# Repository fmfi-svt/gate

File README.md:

This repo is no longer used -- see [github.com/fmfi-svt-deadlock](https://github.com/fmfi-svt-deadlock) for Project Deadlock (formerly Project Gate).

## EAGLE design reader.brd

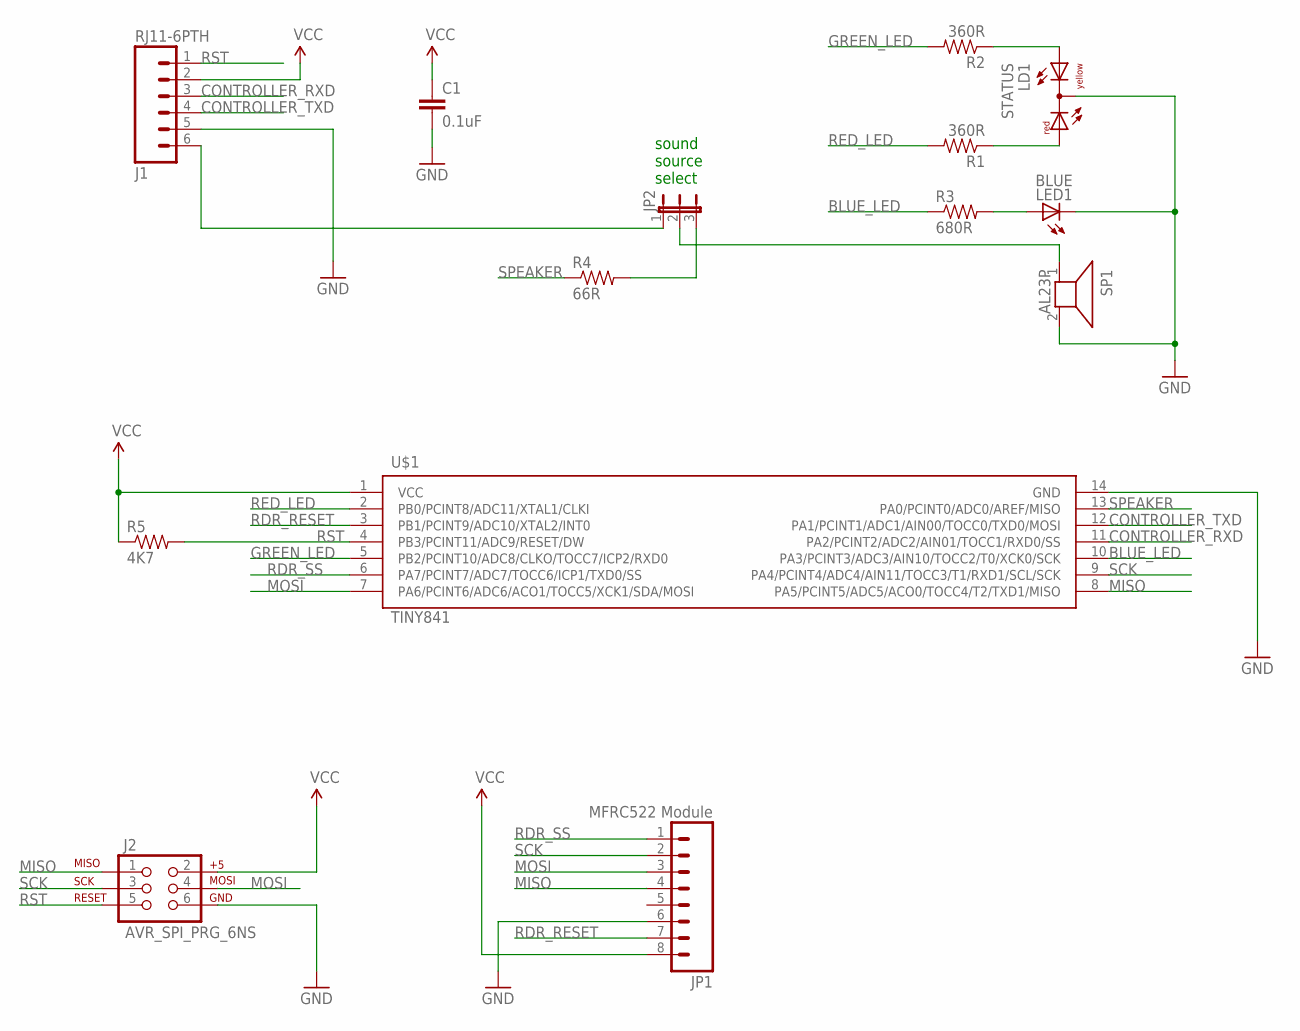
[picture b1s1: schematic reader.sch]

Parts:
C1: 0.1uF; CAP-PTH-SMALL-KIT
J1: RJ11-6PTH; RJ11-6
J2: AVR_SPI_PRG_6NS; 2X3-NS
JP1: MFRC522 Module; 1X08
JP2: JP2E; JP2
LD1: STATUS; DUOLED-C-5MM
LED1: BLUE; LED3MM
R1, R2: 360R; 0805
R3: 680R; 0805
R4: 66R; 0805
R5: 4K7; 0805
SP1: AL23P
U$1: TINY841; SO14

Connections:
BLUE_LED: R3.1, U$1.10 (PA3/PCINT3/ADC3/AIN10/TOCC2/T0/XCK0/SCK)
CONTROLLER_RXD: J1.3, U$1.11 (PA2/PCINT2/ADC2/AIN01/TOCC1/RXD0/SS)
CONTROLLER_TXD: J1.4, U$1.12 (PA1/PCINT1/ADC1/AIN00/TOCC0/TXD0/MOSI)
EXT_SPEAKER: J1.6, JP2.1
GND: C1.2, J1.5, J2.6, JP1.6, LD1.C, LED1.K (C), SP1.2, U$1.14 (GND)
GREEN_LED: R2.2, U$1.5 (PB2/PCINT10/ADC8/CLKO/TOCC7/ICP2/RXD0)
MISO: J2.1, JP1.4, U$1.8 (PA5/PCINT5/ADC5/ACO0/TOCC4/T2/TXD1/MISO)
MOSI: J2.4, JP1.3, U$1.7 (PA6/PCINT6/ADC6/ACO1/TOCC5/XCK1/SDA/MOSI)
unnamed: JP2.2, SP1.1
unnamed: LD1.AR, R1.1
unnamed: LD1.AX (AY), R2.1
unnamed: LED1.A, R3.2
unnamed: JP2.3, R4.2
RDR_RESET: JP1.7, U$1.3 (PB1/PCINT9/ADC10/XTAL2/INT0)
RDR_SS: JP1.1, U$1.6 (PA7/PCINT7/ADC7/TOCC6/ICP1/TXD0/SS)
RED_LED: R1.2, U$1.2 (PB0/PCINT8/ADC11/XTAL1/CLKI)
RST: J1.1, J2.5, R5.2, U$1.4 (PB3/PCINT11/ADC9/RESET/DW)
SCK: J2.3, JP1.2, U$1.9 (PA4/PCINT4/ADC4/AIN11/TOCC3/T1/RXD1/SCL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)
SPEAKER: R4.1, U$1.13 (PA0/PCINT0/ADC0/AREF/MISO)
VCC: C1.1, J1.2, J2.2, JP1.8, R5.1, U$1.1 (VCC)

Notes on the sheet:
sound source select

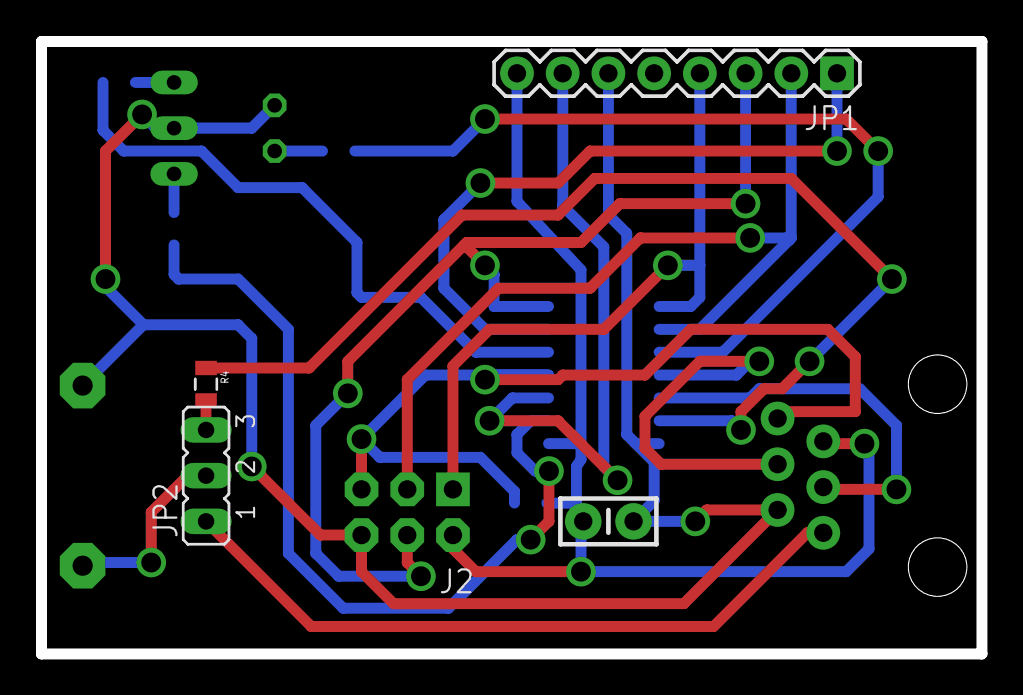
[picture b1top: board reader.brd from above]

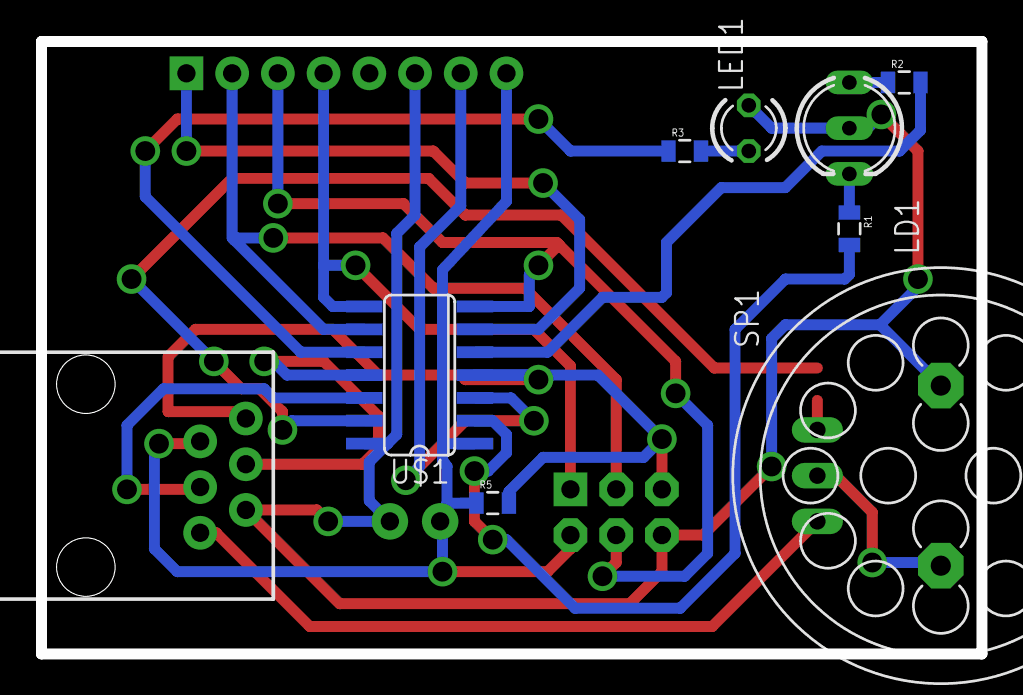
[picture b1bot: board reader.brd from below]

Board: 2 copper layers, 52.2 x 34.0 mm, 14 parts (9 on the bottom side), 20 nets.

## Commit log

2014-10-27 Add .gitignore
2014-10-27 Add SparkFun Eagle libraries submodule
2014-10-27 Add ATTiny841 library
2014-10-28 Add draft of reader schematic
2014-10-31 add README
2014-10-31 initial commit (create branch)
2014-11-01 add links to branches to README
2014-11-01 Connect speaker directly to the main bus, connect rst
2014-11-01 Add option for sound source selection
2014-11-01 Add ISP header, minor layout modifications
2014-11-02 Change speaker footprint for the correct one
2014-11-02 Add PCB draft
2014-11-08 Change sound source select jumpers to a single 3-pin jumper
2014-11-09 Route reader board prototype
2014-11-10 Move the reader connector to the top of the board, reroute accordingly
2015-01-05 Add LICENSE
2015-01-05 Update wiki link
2015-01-05 echo server
2015-01-05 add requirements.txt, update README
2015-01-05 add config.py.example; gitignore config.py
2015-01-06 add database (dependencies + dummy call)
2015-01-06 make simpleclient.py executable
2015-01-06 add manage.py and update README
2015-01-06 fix typo
2015-01-06 make simpleclient.py accept commandline parameters
2015-01-06 config through environment (+ manage.py reads .env); update README
2015-01-06 rename stuff somewhat
2015-01-07 a proper package
2015-01-07 review-induced fixes
2015-01-07 complete rewrite of manage.py
2015-01-07 a little less stupidly implemented walk_actions
2015-04-08 link to fmfi-svt-deadlock in README

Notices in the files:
parts and their libraries:
SparkFun-Capacitors: Licensing: Creative Commons ShareAlike 4.0 International - https://creativecommons.org/licenses/by-sa/4.0
